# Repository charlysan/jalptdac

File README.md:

# jalptdac

Just Another LPT DAC

## Table Of Contents
- [Introduction](#introduction)
- [Design](#design)
- [Schematics (Kicad and Gerber files)](#schematics-kicad-and-gerber-files)
- [Build](#build)
  - [Option #1 (MODPLAY PRO Recommendation)](#option-1-modplay-pro-recommendation)
  - [Option #2 (COVOX)](#option-2-covox)
- [Pictures and videos](#pictures-and-videos)
- [References](#references)

## Introduction

JALPTDAC is a minimalist LPT R-2R DAC that could be assembled within a DSUB-25 connector case. The initial design was inspired by the 1994 [COMPUSOUND interface](https://raw.githubusercontent.com/wiki/charlysan/jalptdac/images/magazine.jpg). The latter appears to be an implementation of the MODPLAY PRO Hardware recommendation:

## Design

The design is somehow flexible, allowing you to choose from several alternatives:

1. Solder a cable to the output and enclose the PCB within a case (like COMPUSOUND)
2. Add a 3.5 female plug connector (and use it without the case)
3. Implement MODPLAY PRO approach (R = 10K)
4. Implement original Covox design (R = 100K)

## Schematics (Kicad and Gerber files)

You can find Kicad files under [./kicad](./kicad/) folder, and Gerber files can be found [here](./kicad/v0.1/gerber/).

## Build

You will need to use high precision resistors (>= 1% tolerance). 

### Option #1 (MODPLAY PRO Recommendation)

| component | Value             | Mouser ID                                    | Notes                      |
|-----------|-------------------|----------------------------------------------|----------------------------|
| R0-R8     | 20K - 0.1%        | [ERA-6AEB203V](https://mou.sr/48EkaXj)       |                            |
| R9-R16    | 10K - 0.1%        | [ERA-6AEB103V](https://mou.sr/3tSAFQK)       |                            |
| R17       | N/A               |                                              |                            |
| R18       | 0 Ohms            | [RC0805JR-100RL](https://mou.sr/427Xlci)     | (Optional - for dual mono) |
| R19       | N/A               |                                              |                            |
| C1        | 0.1 µF (Polarized)| [T489A104M035ATE20K](https://mou.sr/48ZVXur) |                            |
| C2        | 0.01 µF           | [C0805C103J5RAC7025](https://mou.sr/48YnrR3) |                            |
| J2        | 3.5 Audio Jack    | [SJ-3524-SMT-TR](https://mou.sr/3SrcnWj)     |         (Optional)         |

### Option #2 (COVOX)

| component | Value             | Mouser ID                                    | Notes                      |
|-----------|-------------------|----------------------------------------------|----------------------------|
| R0-R7     | 200K - 0.1%       | [ERA-6AEB203V](https://mou.sr/48EkaXj)       |                            |
| R8        | N/A               |                                              |                            |
| R9-R15    | 100K - 0.1%       | [ERA-6AEB103V](https://mou.sr/3tSAFQK)       |                            |
| R16       | 0 Ohms            | [RC0805JR-100RL](https://mou.sr/427Xlci)     |                            |
| R17       | 24K               | [6AEB243V](https://mou.sr/424skpI)           |                            |
| R18       | 0 Ohms            | [RC0805JR-100RL](https://mou.sr/427Xlci)     | (Optional - for dual mono) |
| R19       | 0 Ohms            | [RC0805JR-100RL](https://mou.sr/427Xlci)     |                            |
| C1        | N/A               |                                              |                            |
| C2        | 5100 pF           | [C0805C512F4HACAUTO](https://mou.sr/48FHVhY) |                            |
| J2        | 3.5 Audio Jack    | [SJ-3524-SMT-TR](https://mou.sr/3SrcnWj)     |         (Optional)         |

**Note**: If you decide to use a 3.5 female plug, you can choose between mono and dual-mono output; for dual-mono just short R18 (or add a 0 Ohms resistor)

## Pictures and videos

[Wiki section](https://github.com/charlysan/jalptdac/wiki) includes some pictures and examples.

## References

- [The Covox Years](https://scalibq.wordpress.com/2017/11/28/the-covox-years/)
- [DOScember Making Covox/DAC Hardware and Software](https://www.youtube.com/watch?v=DfNsAK710kQ)
- [Silly Sound Bastard](https://www.youtube.com/watch?v=DKLKtH_rQJU)

**Special thanks to**: [Scali](https://scalibq.wordpress.com/author/scalibq/page/2/), [CallousCoder](https://www.youtube.com/@CallousCoder), & [Necroware](https://www.youtube.com/@necro_ware)

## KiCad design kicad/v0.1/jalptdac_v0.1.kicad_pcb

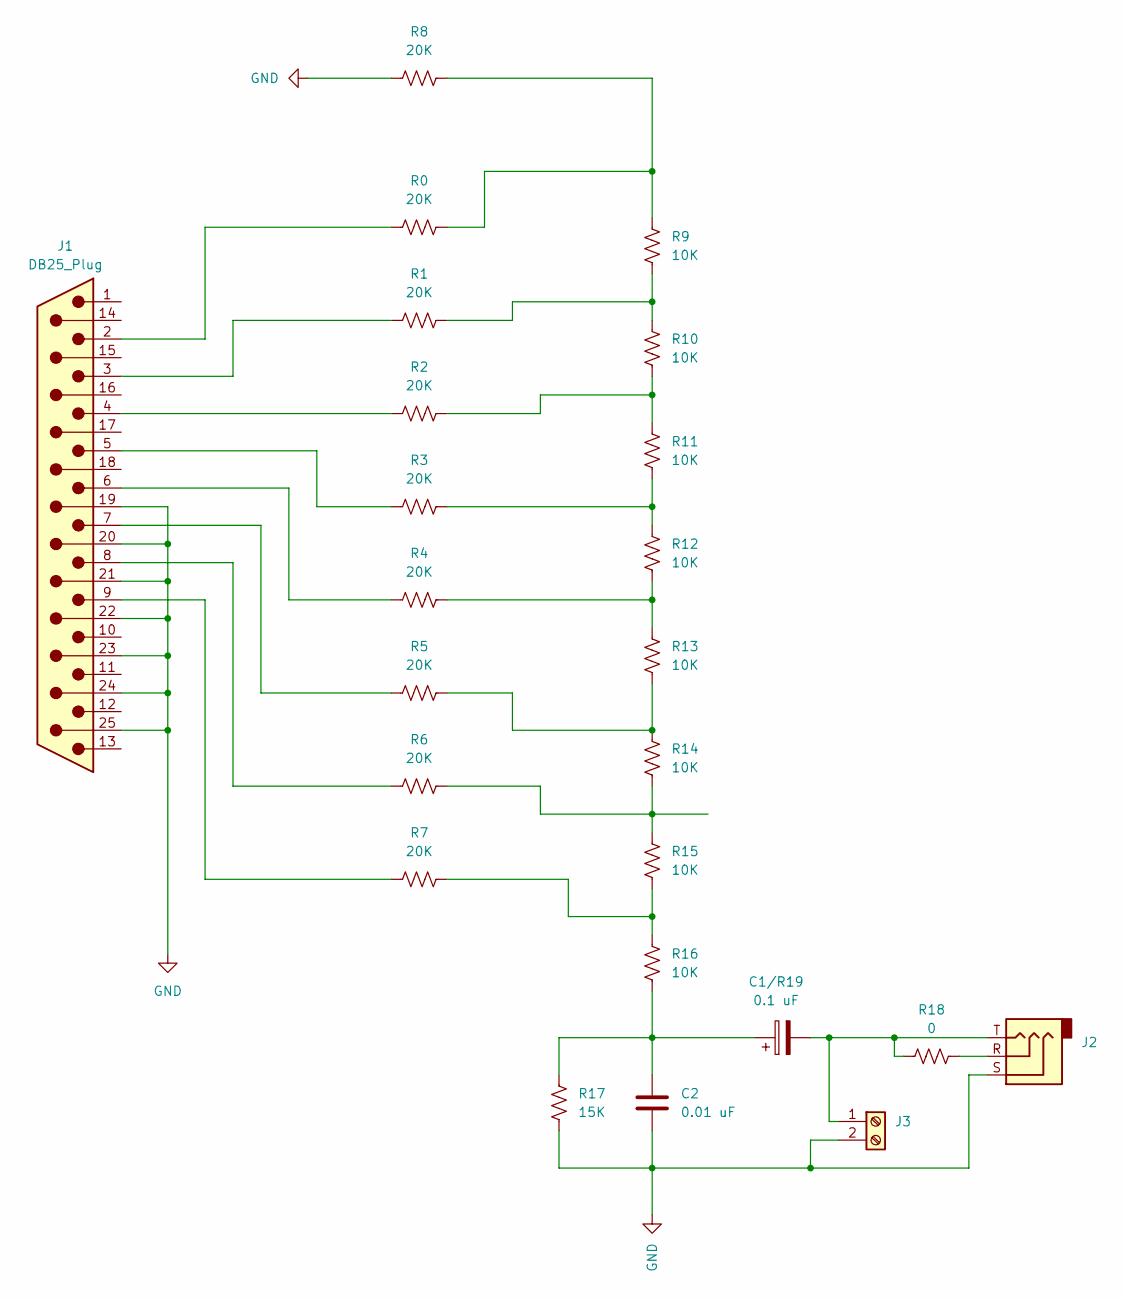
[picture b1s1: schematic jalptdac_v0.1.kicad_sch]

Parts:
C1/R19: 0.1 uF; CP_EIA-3216-10_Kemet-I_Pad1.58x1.35mm_HandSolder
C2: 0.01 uF; C_0805_2012Metric_Pad1.18x1.45mm_HandSolder
J1: DB25_Plug; DSUB-25_Male_EdgeMount_P2.77mm
J2: AudioJack3; Jack_3.5mm_CUI_SJ-3523-SMT_Horizontal
J3: Connector; SolderWire-0.75sqmm_1x02_P4.8mm_D1.25mm_OD2.3mm
R0, R1, R2, R3, R4, R5, R6, R7, R8: 20K; R_0805_2012Metric
R9, R10, R11, R12, R13, R14, R15, R16: 10K; R_0805_2012Metric
R17: 15K; R_0805_2012Metric
R18: 0; R_0805_2012Metric

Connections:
GND: C2.2, J1.19, J1.20, J1.21, J1.22, J1.23, J1.24, J1.25, J2.S, J3.2, R8.1, R17.1
unnamed: C1/R19.1, C2.1, R16.1, R17.2
unnamed: J1.2, R0.1
unnamed: J1.3, R1.1
unnamed: J1.4, R2.1
unnamed: J1.5, R3.1
unnamed: J1.6, R4.1
unnamed: J1.7, R5.1
unnamed: J1.8, R6.1
unnamed: J1.9, R7.1
unnamed: J2.R, R18.1
unnamed: C1/R19.2, J2.T, J3.1, R18.2
unnamed: R0.2, R8.2, R9.2
unnamed: R1.2, R9.1, R10.2
unnamed: R2.2, R10.1, R11.2
unnamed: R3.2, R11.1, R12.2
unnamed: R4.2, R12.1, R13.2
unnamed: R5.2, R13.1, R14.2
unnamed: R6.2, R14.1, R15.2
unnamed: R7.2, R15.1, R16.2

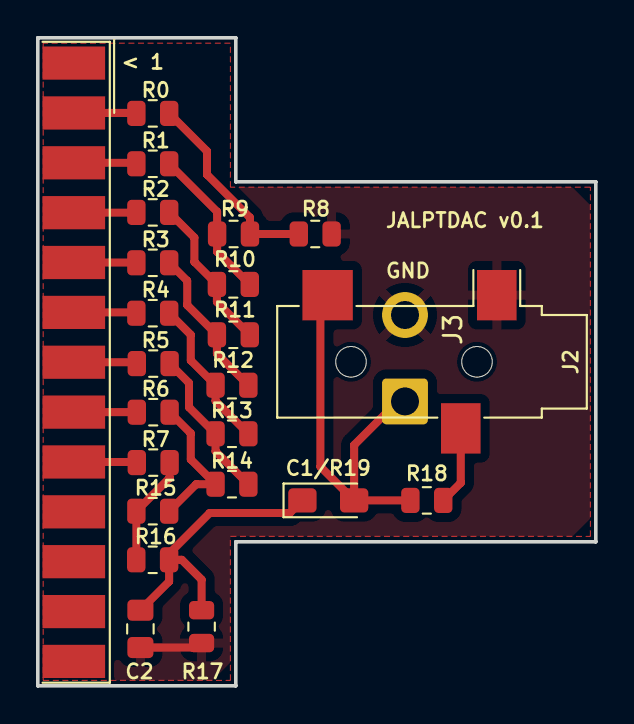
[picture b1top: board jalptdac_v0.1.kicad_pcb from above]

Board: 2 copper layers, 31.0 x 36.0 mm, 24 parts (0 on the bottom side), 20 nets.

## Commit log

2024-01-23 Add Readme and kicad files
